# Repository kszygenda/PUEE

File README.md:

# PUEE
PUT course "design of electrical and electronic systems" projects

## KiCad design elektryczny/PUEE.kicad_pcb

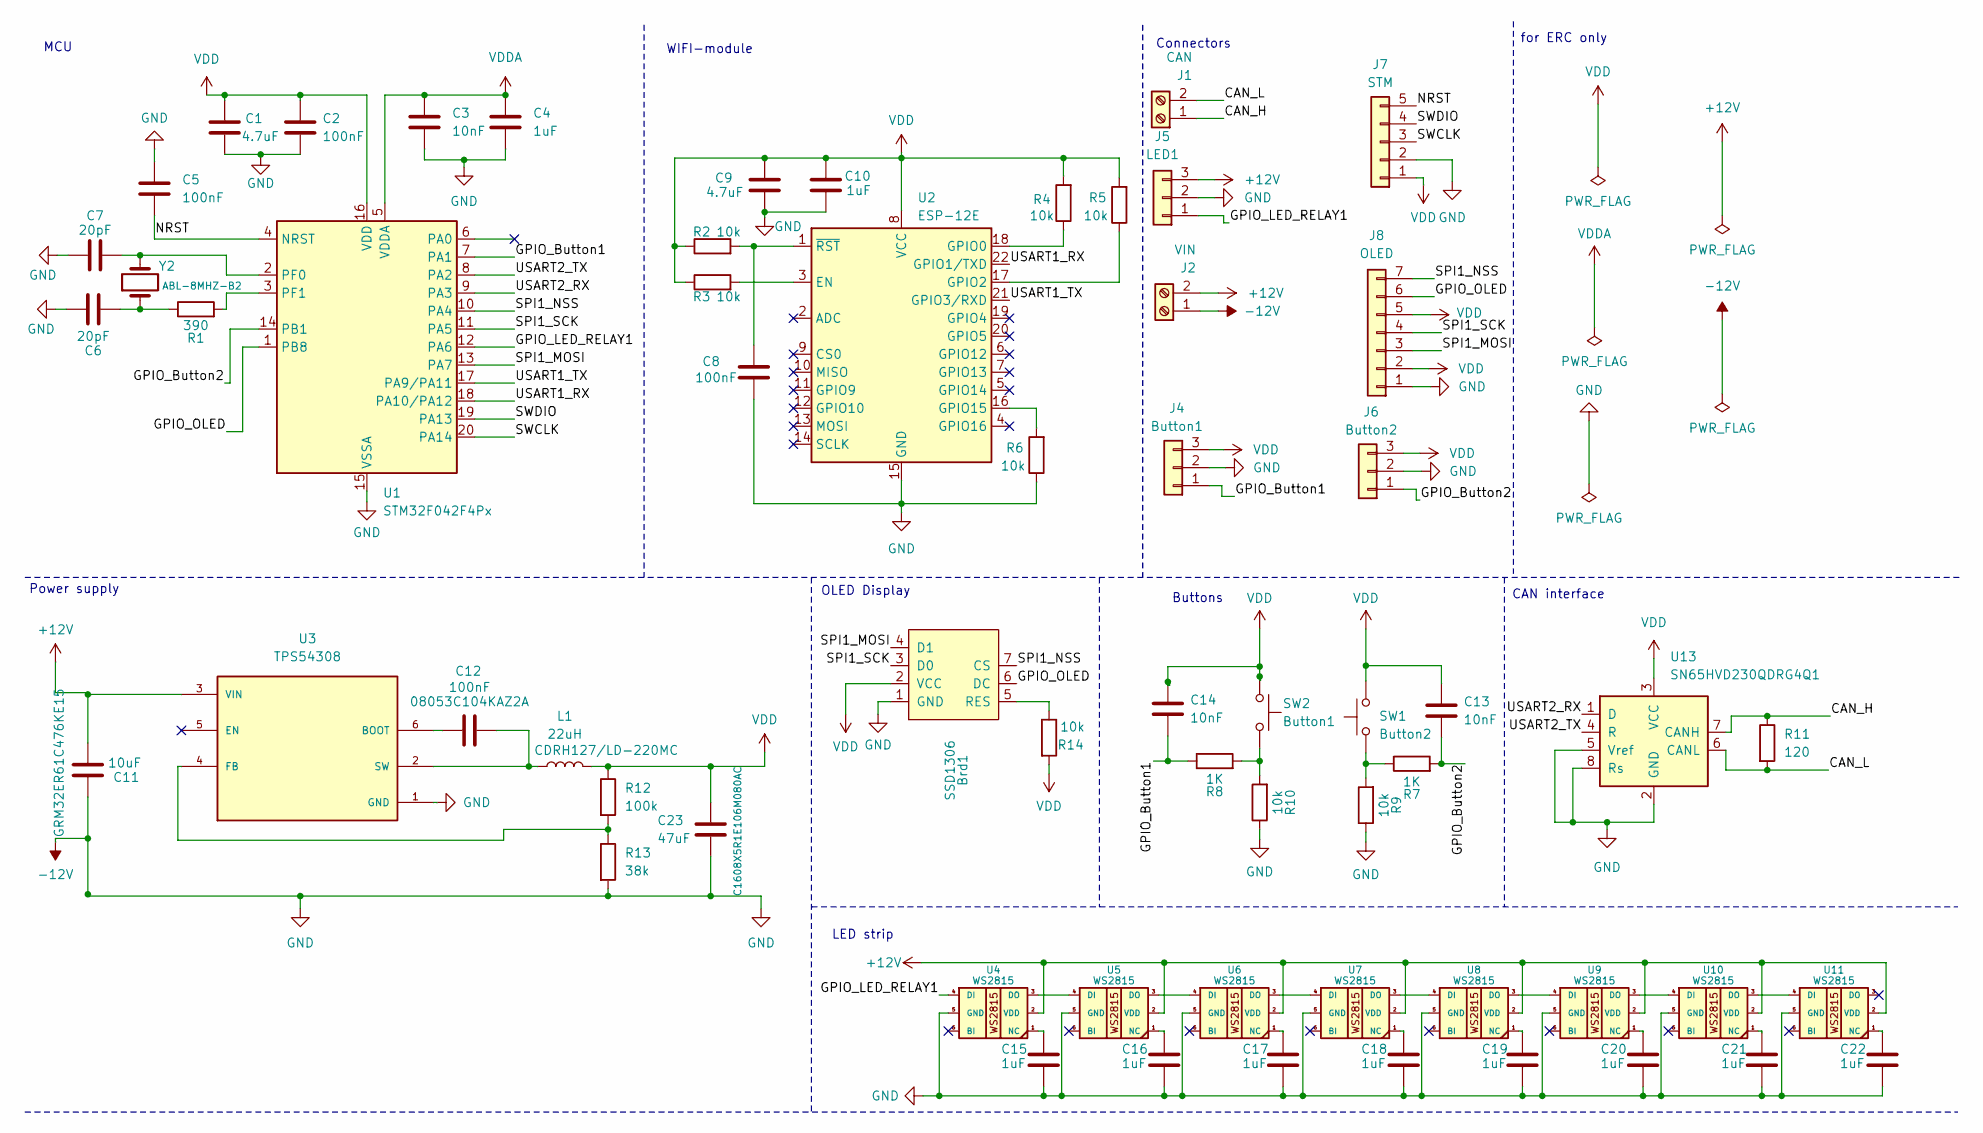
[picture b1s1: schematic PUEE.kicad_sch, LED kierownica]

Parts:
Brd1: SSD1306; Adafruit_SSD1306
C1, C9: 4.7uF; C_0805_2012Metric
C2, C5, C8, C12: 100nF; C_0805_2012Metric
C3, C13, C14: 10nF; C_0805_2012Metric
C4, C10, C15, C16, C17, C18, C19, C20, C21, C22: 1uF; C_0805_2012Metric
C6, C7: 20pF; C_0805_2012Metric
C11: 10uF; C_1210_3225Metric
C23: 47uF; C_0603_1608Metric
J1: CAN; PhoenixContact_MCV_1,5_2-G-3.5_1x02_P3.50mm_Vertical
J2: VIN; PhoenixContact_MCV_1,5_2-G-3.5_1x02_P3.50mm_Vertical
J4: Button1; PinHeader_1x03_P2.54mm_Vertical
J5: LED1; PinHeader_1x03_P2.54mm_Vertical
J6: Button2; PinHeader_1x03_P2.54mm_Vertical
J7: STM; PinHeader_1x05_P2.54mm_Vertical
J8: OLED; PinHeader_1x07_P2.54mm_Vertical
L1: 22uH; L_12x12mm_H8mm
R1: 390; R_0805_2012Metric
R2, R3, R4, R5, R6, R9, R10, R14: 10k; R_0805_2012Metric
R7, R8: 1K; R_0805_2012Metric
R11: 120; R_0805_2012Metric
R12: 100k; R_0805_2012Metric
R13: 38k; R_0805_2012Metric
SW1: Button2; SW_SPST_PTS647_Sx38
SW2: Button1; SW_SPST_PTS647_Sx38
U1: STM32F042F4Px; TSSOP-20_4.4x6.5mm_P0.65mm
U2: ESP-12E
U3: TPS54308; SOT-23-6; PARTREV A
U4, U5, U6, U7, U8, U9, U10, U11: WS2815; LED_WS2812_PLCC6_5.0x5.0mm_P1.6mm
U13: SN65HVD230QDRG4Q1; SOIC-8_3.9x4.9mm_P1.27mm
Y2: ABL-8MHZ-B2; ABL-8.000MHZ-B2_ABR

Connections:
+12V: C11.2, J2.2, J5.3, U3.3 (VIN), U4.2 (VDD), U5.2 (VDD), U6.2 (VDD), U7.2 (VDD), U8.2 (VDD), U9.2 (VDD), U10.2 (VDD), U11.2 (VDD)
-12V: Brd1.1 (GND), C1.2, C2.2, C3.2, C4.2, C5.2, C6.2, C7.2, C8.1, C9.1, C10.1, C11.1, C15.2, C16.2, C17.2, C18.2, C19.2, C20.2, C21.2, C22.2, C23.2, J2.1, J7.2, R6.1, R9.1, R10.1, R13.2, U1.15 (VSSA), U2.15 (GND), U3.1 (GND), U4.5 (GND), U5.5 (GND), U6.5 (GND), U7.5 (GND), U8.5 (GND), U9.5 (GND), U10.5 (GND), U11.5 (GND), U13.2 (GND), U13.5 (Vref), U13.8 (Rs)
/CAN_H: J1.1, R11.1, U13.7 (CANH)
/CAN_L: J1.2, R11.2, U13.6 (CANL)
/GPIO_Button1: C14.2, R8.1, U1.7 (PA1)
/GPIO_Button2: C13.2, R7.2, U1.14 (PB1)
/GPIO_LED_RELAY1: J5.1, U1.12 (PA6), U3.12, U4.4 (DI)
/GPIO_OLED: Brd1.6 (DC), U1.1 (PB8)
/NRST: C5.1, J7.5, U1.4 (NRST)
/SPI1_MOSI: Brd1.4 (D1), J8.3, U1.13 (PA7), U3.13
/SPI1_NSS: Brd1.7 (CS), J8.7, U1.10 (PA4), U3.10
/SPI1_SCK: Brd1.3 (D0), J8.4, U1.11 (PA5), U3.11
/SWCLK: J7.3, U1.20 (PA14)
/SWDIO: J7.4, U1.19 (PA13)
/USART1_RX: U1.18 (PA10/PA12), U2.22 (GPIO1/TXD)
/USART1_TX: U1.17 (PA9/PA11), U2.21 (GPIO3/RXD)
/USART2_RX: U1.9 (PA3), U13.1 (D)
/USART2_TX: U1.8 (PA2), U13.4 (R)
unnamed: Brd1.5 (RES), R14.1
unnamed: C6.1, R1.1, Y2.1
unnamed: R7.1, R9.2, SW1.1
unnamed: R8.2, R10.2, SW2.2
unnamed: C7.1, U1.2 (PF0), Y2.2
unnamed: R1.2, U1.3 (PF1)
unnamed: R3.2, U2.3 (EN)
unnamed: R4.1, U2.18 (GPIO0)
unnamed: R5.1, U2.17 (GPIO2)
unnamed: R6.2, U2.16 (GPIO15)
unnamed: C8.2, R2.2, U2.1 (~RST)
unnamed: C12.1, U3.6 (BOOT)
unnamed: R12.2, R13.1, U3.4 (FB)
unnamed: C12.2, L1.1, U3.2 (SW)
unnamed: U4.3 (DO), U5.4 (DI)
unnamed: C15.1, U4.1 (NC)
unnamed: U5.3 (DO), U6.4 (DI)
unnamed: C16.1, U5.1 (NC)
unnamed: U6.3 (DO), U7.4 (DI)
unnamed: C17.1, U6.1 (NC)
unnamed: U7.3 (DO), U8.4 (DI)
unnamed: C18.1, U7.1 (NC)
unnamed: U8.3 (DO), U9.4 (DI)
unnamed: C19.1, U8.1 (NC)
unnamed: C20.1, U9.1 (NC)
unnamed: U9.3 (DO), U10.4 (DI)
unnamed: U10.3 (DO), U11.4 (DI)
unnamed: C21.1, U10.1 (NC)
unnamed: C22.1, U11.1 (NC)
VDD: Brd1.2 (VCC), C1.1, C2.1, C9.2, C10.2, C13.1, C14.1, C23.1, J7.1, L1.2, R2.1, R3.1, R4.2, R5.2, R12.1, R14.2, SW1.2, SW2.1, U1.16 (VDD), U2.8 (VCC), U13.3 (VCC)
VDDA: C3.1, C4.1, U1.5 (VDDA)

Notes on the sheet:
OLED Display
for ERC only
WIFI-module
Connectors
MCU
CAN interface
LED strip
Power supply
Buttons

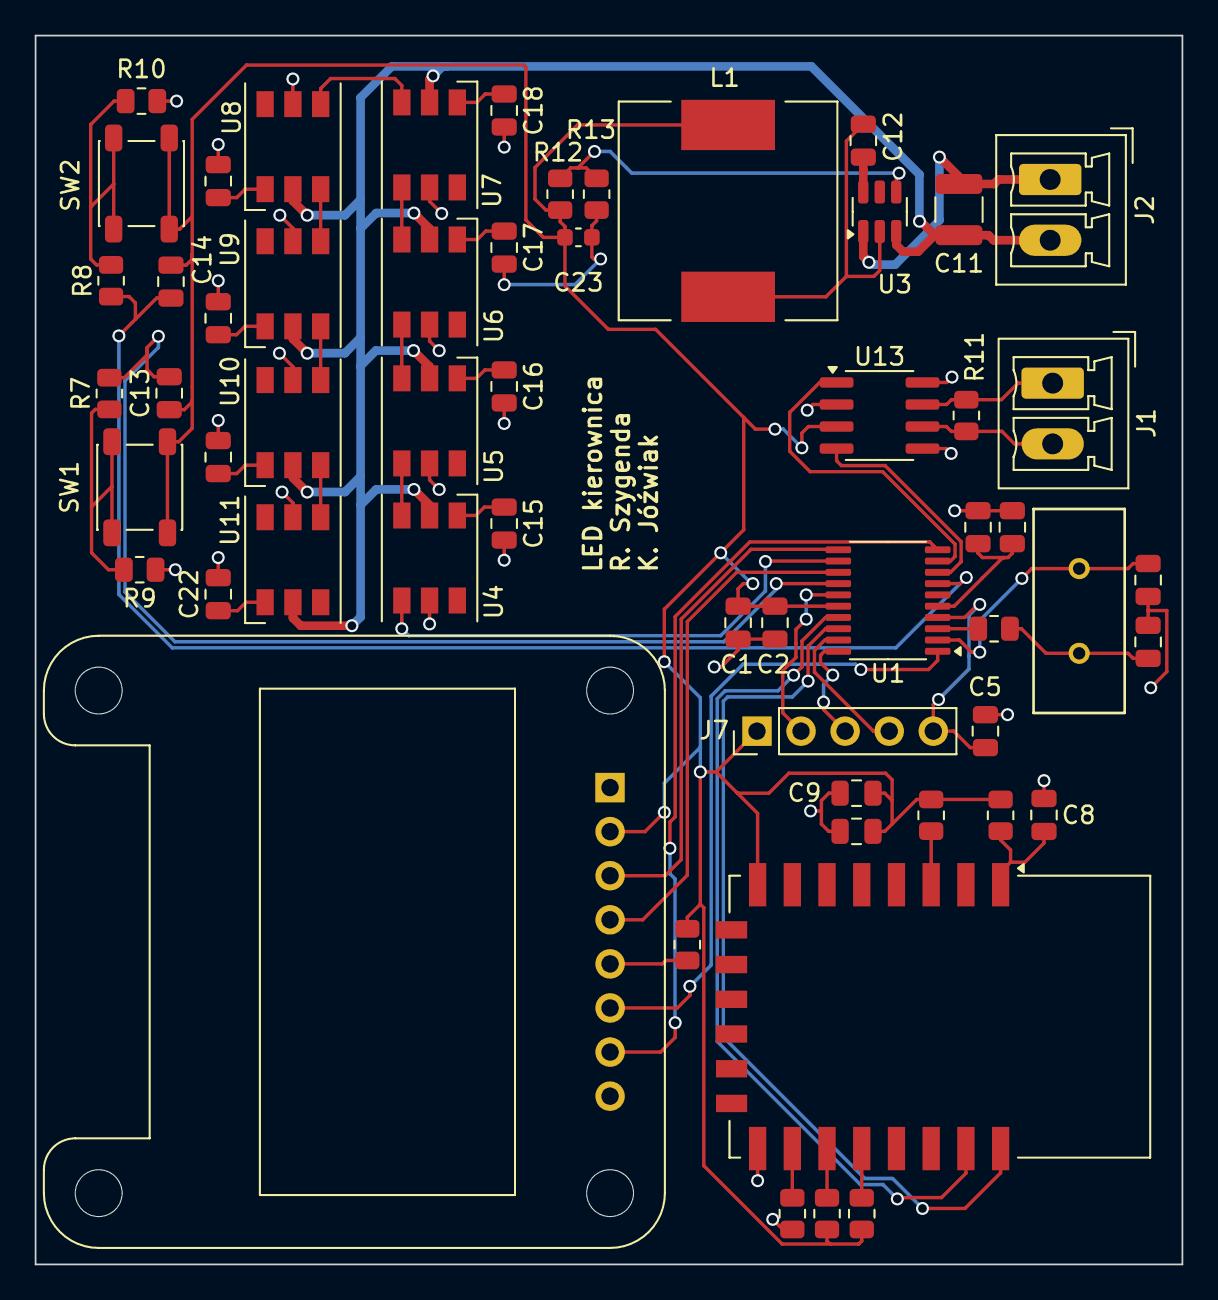
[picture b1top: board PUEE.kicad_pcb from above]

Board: 2 copper layers, 66.1 x 70.8 mm, 57 parts (0 on the bottom side), 49 nets.

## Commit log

2024-11-01 zmiana folderów
2024-11-01 TJA1050 added
2024-11-02 Wstępny schemat elektroniczny
2024-11-03 glowny schemat + MCU WIFI PSU Components
2024-11-03 pinout STM
2024-11-06 Import symbolu LED
2024-11-12 full schematic + blueprints
2024-11-18 poprawa schematu, wymiary sciezek wylotek, pcb film 3.
2024-12-04 poprawki pcb
2024-12-10 polaczenia pcb czesc 1/2
2024-12-11 polaczenia attempt 1, do poprawki
2024-12-14 finalizacja projektu v1.0
